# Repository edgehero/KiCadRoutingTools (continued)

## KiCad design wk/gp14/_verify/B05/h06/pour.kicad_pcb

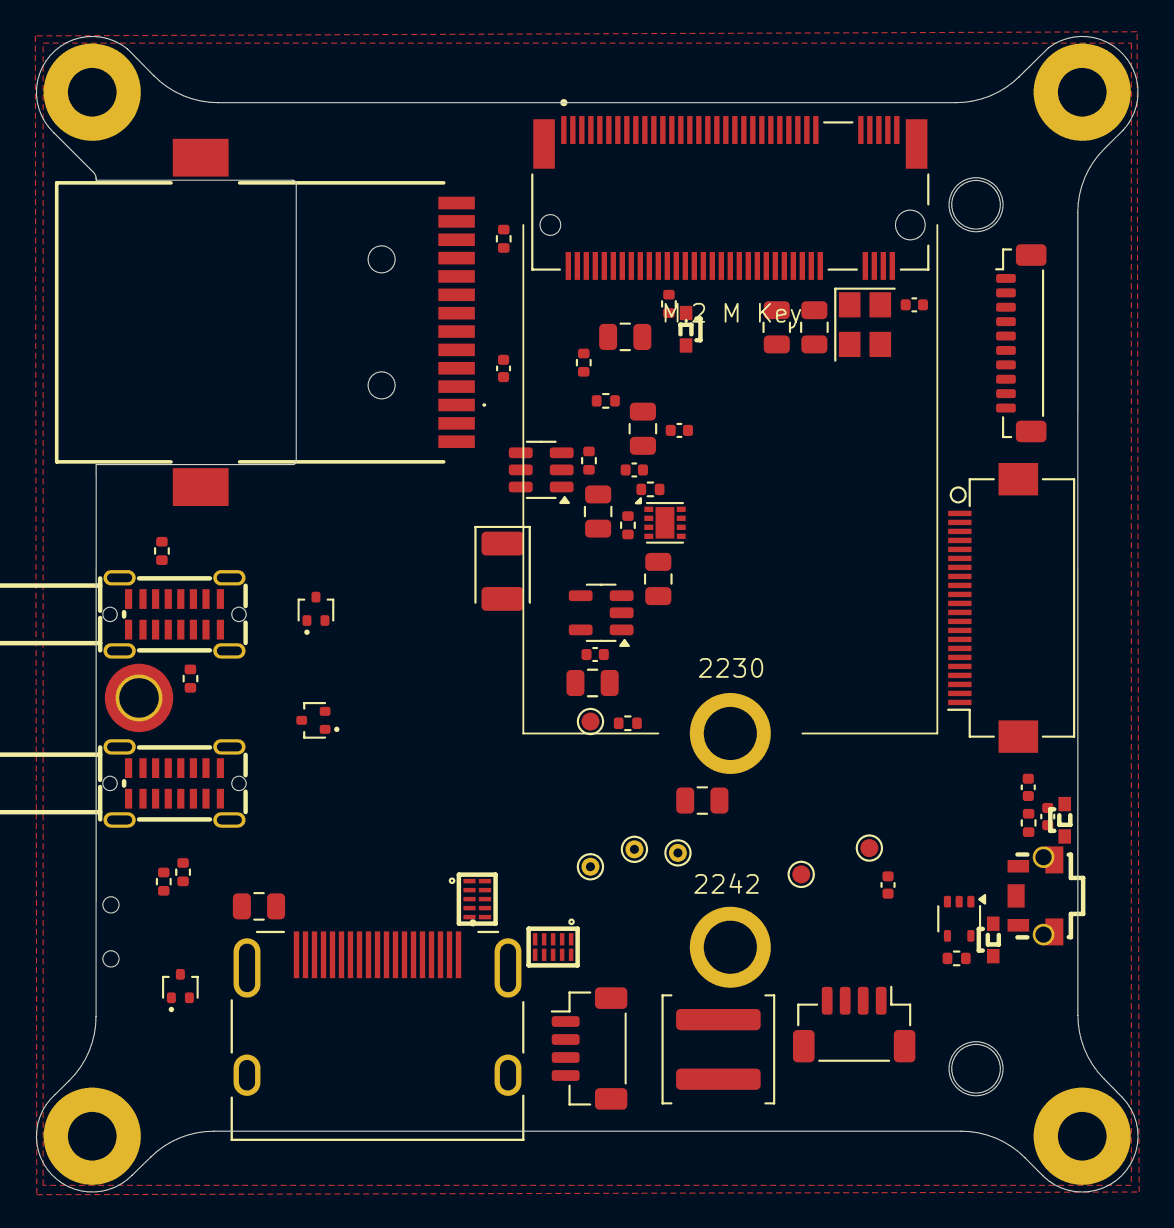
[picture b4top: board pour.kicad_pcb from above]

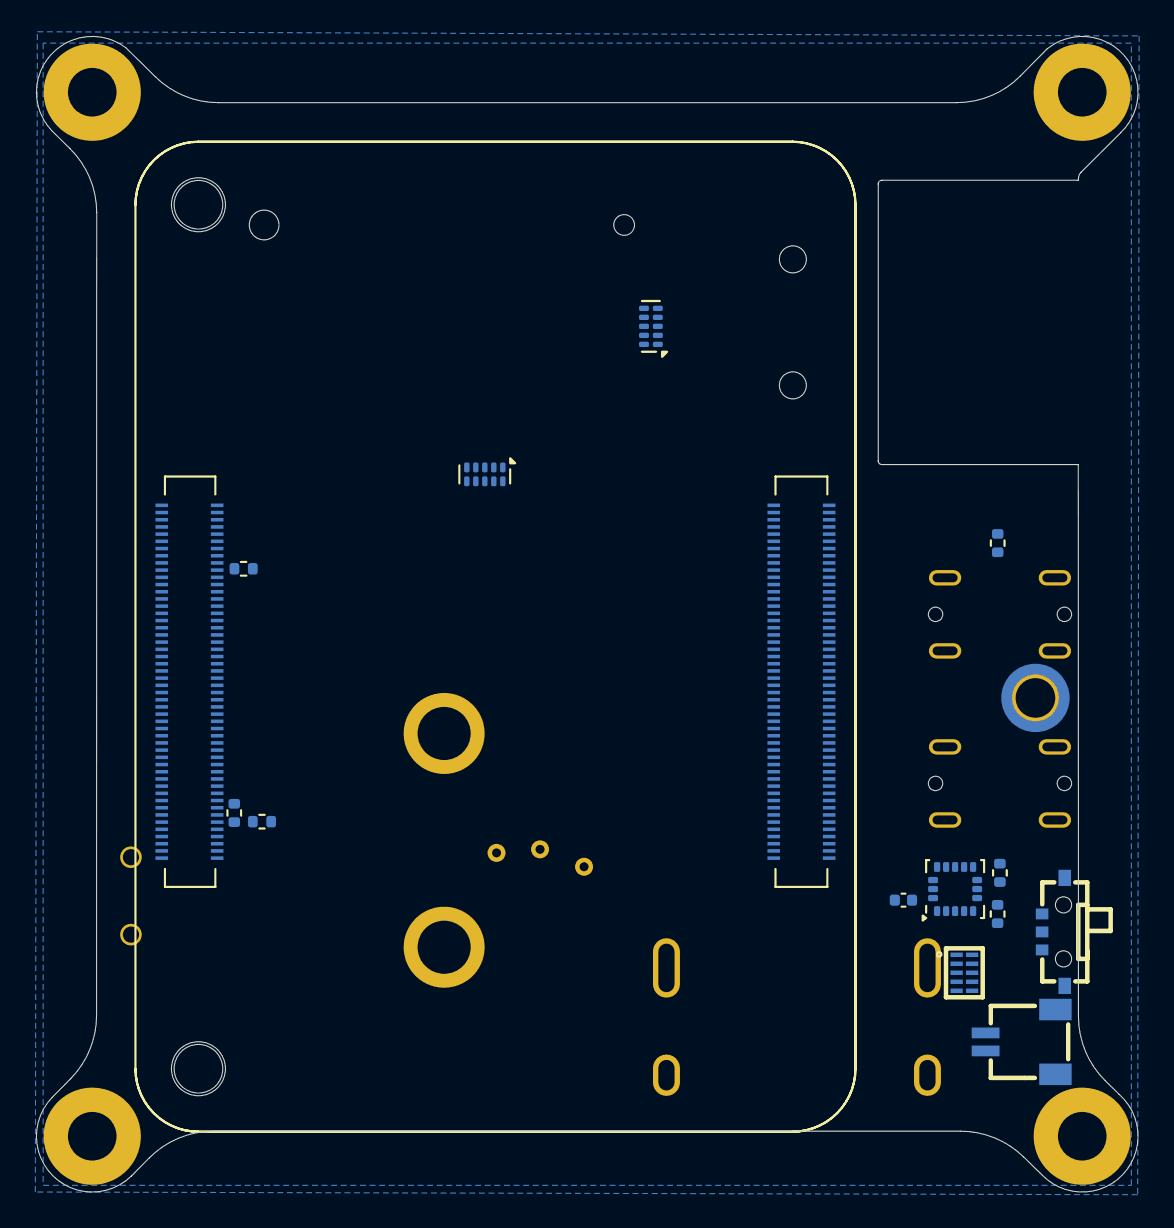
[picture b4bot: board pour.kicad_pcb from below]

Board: 6 copper layers, 61.2 x 64.2 mm, 84 parts (15 on the bottom side), 95 nets, no tracks yet.

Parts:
C101, C102, C401, C501, C502, C503, C706, C712: 100n; C_0402_1005Metric
C601: 4u7; C_0805_2012Metric
C701, C703, C704, C705, C708, C709, C710, C711: 10u; C_0805_2012Metric
C702: 100uF; CP_EIA-3528-21_Kemet-B
C707: 4.7nF; C_0402_1005Metric
CN1: SM02B-SRSS-TB (LF)(SN); CONN-SMD_2P-P1.00_SM02B-SRSS-TB-LF-SN
D101, D502, D701: RCLAMP0502BA; SOT-416
D401, D402, D403: PUSB3F96X; DFN2510A-10_L2.5-W1.0-P0.50-BL
D605, D606, D702: GREEN; LED-SMD_L1.7-W0.6-RD
H101: MountingHole_Pad; MountingHole_2.2mm_M2_DIN965_Pad_TopBottom
H102, H103, H104, H105: MountingHole_Pad; MountingHole_2.7mm_Pad
J1: GLPLX-SMT-188S7; GLPLXSMT188S7QQYG
J101: TYPEC-305-ACP16H458; USB-C-SMD_TYPEC-305-ACP16H458
J501: GT-HD001B-CNNG1; EDAC 690-019-298-412
J502: I2C; JST_SH_BM04B-SRSS-TB_1x04-1MP_P1.00mm_Vertical
J503: SPI; JST_SUR_BM10B-SURS-TF_1x10-1MP_P0.80mm_Vertical
J601: JST_SHBM04B-SRSS-TB; JST_SH_BM04B-SRSS-TB_1x04-1MP_P1.00mm_Vertical
J701: Bus_M.2_Socket_M; M.2 M Key socket_2230_2242
J802: Conn_01x22_Female; Hirose_FH12-22S-0.5SH_1x22-1MP_P0.50mm_Horizontal
L701: 2.2uH; L_Coilcraft_XAL5030-XXX
M701, M702: M.2 Solder Nut; MountingHole_3mm_Pad
Module301: ComputeModule5-CM5; Raspberry-Pi-5-Compute-Module_GPIO
Module302: ComputeModule5-CM5; Raspberry-Pi-5-Compute-Module_HSS
R101, R501, R502, R605, R606, R706, R707: 2k2; R_0402_1005Metric
R102, R103, R403: 0R; R_0402_1005Metric
R104, R107, R108, R705: 10k; R_0402_1005Metric
R401, R402: 470R; R_0402_1005Metric
R701: 15k; R_0402_1005Metric
R702, R703: 22k; R_0402_1005Metric
R704: 100k; R_0402_1005Metric
SW101: MK-11C04-G013; SW-SMD_MK-11C04-G013
SW501: TS-1010A-B; SW-SMD_TS-1010A-B
TP101: VBUS; TestPoint_Pad_D1.0mm
TP102: +5V_PI; TestPoint_Pad_D1.0mm
TP103: +3V3_PI; TestPoint_Pad_D1.0mm
TP104, TP105, TP106: GND; TestPoint_THTPad_D1.0mm_Drill0.5mm
U1: LIS3DH; LGA-16_3x3mm_P0.5mm_LayoutBorder3x5y
U401, U402: TPD4EUSB30; USON-10_2.5x1.0mm_P0.5mm
U405: STMPS2151STR; SOT-23-5
U602: SN74LVC1G14DBVR; SOT-353_SC-70-5
U701: AP22653W6; SOT-23-6
U702: AP3441SHE-7B; DFN-8-1EP_2x2mm_P0.5mm_EP1.05x1.75mm
U703: ASEK-32.768KHZ-L-R-T; Crystal_SMD_3225-4Pin_3.2x2.5mm
USB701: TYPEC-305-ACP16H458; USB-C-SMD_TYPEC-305-ACP16H458

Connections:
+1V8: Module301.88 (+1.8v_(Output)), Module301.90 (+1.8v_(Output)), R103.1
+3V3_PI: C503.1, C601.1, J1.12 (A_GREEN), J1.14 (A_YELLOW), J502.4, J503.1, J802.22, Module301.84 (+3.3v_(Output)), Module301.86 (+3.3v_(Output)), R102.1, R107.2, R501.1, R502.1, TP103.1, U1.1 (VDD_IO), U1.14 (VDD)
+5V: C101.1, C102.1, C501.1, C701.1, C704.1, C705.1, C706.1, D605.2 (A), D606.2 (A), J101.A4 (VBUS), J101.A9 (VBUS), J101.B4 (VBUS), J101.B9 (VBUS), J601.1, Module301.77 (+5v_(Input)), Module301.79 (+5v_(Input)), Module301.81 (+5v_(Input)), Module301.83 (+5v_(Input)), Module301.85 (+5v_(Input)), Module301.87 (+5v_(Input)), R101.1, R702.2, R703.2, TP101.1, TP102.1, U405.4 (EN), U405.5 (VIN), U602.5 (VCC), U701.1 (IN), U702.3 (VIN)
+BATT: CN1.1, Module301.76 (VBAT)
/CC1: J101.A5 (CC1), Module301.94 (CC1)
/CC2: J101.B5 (CC2), Module301.96 (CC2)
/CM5/BL_GPIO24: J503.7, Module301.45 (GPIO24)
/CM5/CAM_GPIO0: J802.17, Module301.97 (CAM_GPIO0)
/CM5/CAM_GPIO1: J802.18, Module301.100 (CAM_GPIO1)
/CM5/CS_GPIO18: J503.5, Module301.49 (GPIO18)
/CM5/DC_GPI25: J503.3, Module301.41 (GPIO25)
/CM5/DPHY0_P.C_N: J802.8, Module302.127 (MIPI0_C_N)
/CM5/DPHY0_P.C_P: J802.9, Module302.129 (MIPI0_C_P)
/CM5/DPHY0_P.D0_N: J802.2, Module302.115 (MIPI0_D0_N)
/CM5/DPHY0_P.D0_P: J802.3, Module302.117 (MIPI0_D0_P)
/CM5/DPHY0_P.D1_N: J802.5, Module302.121 (MIPI0_D1_N)
/CM5/DPHY0_P.D1_P: J802.6, Module302.123 (MIPI0_D1_P)
/CM5/DPHY0_P.D2_N: J802.11, Module302.133 (MIPI0_D2_N)
/CM5/DPHY0_P.D2_P: J802.12, Module302.135 (MIPI0_D2_P)
/CM5/DPHY0_P.D3_N: J802.14, Module302.139 (MIPI0_D3_N)
/CM5/DPHY0_P.D3_P: J802.15, Module302.141 (MIPI0_D3_P)
/CM5/EEPROM_nWP: Module301.20 (EEPROM_nWP), R104.2
/CM5/ETH_PI.TRD0_N: J1.3 (TD1-), Module301.10 (Ethernet_Pair0_N), U401.2 (D1-), U401.9
/CM5/ETH_PI.TRD0_P: J1.2 (TD1+), Module301.12 (Ethernet_Pair0_P), U401.1 (D1+), U401.10
/CM5/ETH_PI.TRD1_N: J1.5 (TD2-), Module301.6 (Ethernet_Pair1_N), U401.5 (D2-), U401.6
/CM5/ETH_PI.TRD1_P: J1.4 (TD2+), Module301.4 (Ethernet_Pair1_P), U401.4 (D2+), U401.7
/CM5/ETH_PI.TRD2_N: J1.7 (TD3-), Module301.9 (Ethernet_Pair2_N), U402.2 (D1-), U402.9
/CM5/ETH_PI.TRD2_P: J1.6 (TD3+), Module301.11 (Ethernet_Pair2_P), U402.1 (D1+), U402.10
/CM5/ETH_PI.TRD3_N: J1.9 (TD4-), Module301.5 (Ethernet_Pair3_N), U402.5 (D2-), U402.6
/CM5/ETH_PI.TRD3_P: J1.8 (TD4+), Module301.3 (Ethernet_Pair3_P), U402.4 (D2+), U402.7
/CM5/ETH_nLED_ACTIVITY: Module301.15 (Ethernet_nLED3(3.3v)), R401.1
/CM5/GPIO_VREF: Module301.78 (GPIO_VREF(1.8v/3.3v_Input)), R102.2, R103.2
/CM5/HDMI_PI.CEC: D403.1 (CH1), D403.10 (NC), J501.13 (CEC), Module302.151 (HDMI0_CEC)
/CM5/HDMI_PI.CK_N: D401.5 (CH4), D401.6 (NC), J501.12 (CK-), Module302.190 (HDMI0_CLK_N)
/CM5/HDMI_PI.CK_P: D401.4 (CH3), D401.7 (NC), J501.10 (CK+), Module302.188 (HDMI0_CLK_P)
/CM5/HDMI_PI.D0_N: D401.2 (CH2), D401.9 (NC), J501.9 (D0-), Module302.184 (HDMI0_TX0_N)
/CM5/HDMI_PI.D0_P: D401.1 (CH1), D401.10 (NC), J501.7 (D0+), Module302.182 (HDMI0_TX0_P)
/CM5/HDMI_PI.D1_N: D402.5 (CH4), D402.6 (NC), J501.6 (D1-), Module302.178 (HDMI0_TX1_N)
/CM5/HDMI_PI.D1_P: D402.4 (CH3), D402.7 (NC), J501.4 (D1+), Module302.176 (HDMI0_TX1_P)
/CM5/HDMI_PI.D2_N: D402.2 (CH2), D402.9 (NC), J501.3 (D2-), Module302.172 (HDMI0_TX2_N)
/CM5/HDMI_PI.D2_P: D402.1 (CH1), D402.10 (NC), J501.1 (D2+), Module302.170 (HDMI0_TX2_P)
/CM5/HDMI_PI.HOTPLUG: D403.2 (CH2), D403.9 (NC), J501.19 (HPD/HEAC-), Module302.153 (HDMI0_HOTPLUG)
/CM5/HDMI_PI.SCL: D403.5 (CH4), D403.6 (NC), J501.15 (SCL), Module302.200 (HDMI0_SCL)
/CM5/HDMI_PI.SDA: D403.4 (CH3), D403.7 (NC), J501.16 (SDA), Module302.199 (HDMI0_SDA)
/CM5/MISO_GPIO19: J503.10, Module301.26 (GPIO19)
/CM5/MOSI_GPIO20: J503.9, Module301.27 (GPIO20)
/CM5/PCIE_PI.CLK_N: J701.53 (REFCLKn), Module302.112 (PCIe_CLK_N)
/CM5/PCIE_PI.CLK_P: J701.55 (REFCLKp), Module302.110 (PCIe_CLK_P)
/CM5/PCIE_PI.PWR_EN: Module302.106 (PCIE_PWR_EN), R704.1, U702.7 (EN)
/CM5/PCIE_PI.RX_N: J701.43 (PETp0), Module302.118 (PCIe_RX_N)
/CM5/PCIE_PI.RX_P: J701.41 (PETn0), Module302.116 (PCIe_RX_P)
/CM5/PCIE_PI.TX_N: J701.49 (PERp0), Module302.124 (PCIe_TX_N)
/CM5/PCIE_PI.TX_P: J701.47 (PERn0), Module302.122 (PCIe_TX_P)
/CM5/PCIE_PI.nCLKREQ: J701.52 (~CLKREQ), Module302.102 (PCIe_nCLKREQ)
/CM5/PCIE_PI.nRST: J701.50 (~PERST), Module302.109 (PCIe_nRST)
/CM5/PCIE_PI.nWAKE: J701.54 (~PEWAKE), Module302.104 (PCIE_nWAKE)
/CM5/PI_nLED_PWR: Module301.95 (LED_nPWR), U602.2
/CM5/PWM: J601.2, Module301.19 (FAN_PWM)
/CM5/PWR_BUT: Module301.92 (PWR_BUT), SW501.1
/CM5/RST_GPIO27: J503.4, Module301.48 (GPIO27)
/CM5/SCL0: J802.20, Module301.80 (SCL0)
/CM5/SCLK_GPIO21: J503.8, Module301.25 (GPIO21)
/CM5/SDA0: J802.21, Module301.82 (SDA0)
/CM5/TACHO: J601.4, Module301.16 (FAN_TACHO)
/CM5/USB2P.D_N: D701.2 (K2), Module302.136 (USB3-0-D_N), USB701.A7 (D-), USB701.B7 (D-)
/CM5/USB2P.D_P: D701.1 (K1), Module302.134 (USB3-0-D_P), USB701.A6 (D+), USB701.B6 (D+)
/CM5/VBUS_EN: Module302.111 (VBUS_EN), U701.3 (EN)
/CM5/nLED_ACTIVITY: Module301.21 (LED_nACT), R606.2
/CM5/nLED_SPEED_100_1000: Module301.17 (Ethernet_nLED2(3.3v)), R402.1
/CM5/nRPIBOOT: Module301.93 (nRPIBOOT), SW101.C
/IO/SCL: D502.1 (K1), J502.2, Module301.56 (GPIO3), R502.2, U1.4 (SPC)
/IO/SDA: D502.2 (K2), J502.1, Module301.58 (GPIO2), R501.2, U1.6 (SDI)
/PCIe-M2/FB: C707.2, R705.2, R706.1, U702.1 (FB)
/PCIe-M2/M2_LX: L701.1, U702.6 (LX)
/USB/CC1: R703.1, USB701.A5 (CC1)
/USB/CC2: R702.1, USB701.B5 (CC2)
/USB_C.D_N: D101.2 (K2), J101.A7 (D-), J101.B7 (D-), Module302.103 (USB2_N)
/USB_C.D_P: D101.1 (K1), J101.A6 (D+), J101.B6 (D+), Module302.105 (USB2_P)
GND: C101.2, C102.2, C401.2, C501.2, C502.2, C503.2, C601.2, C701.2, C702.2, C703.2, C704.2, C705.2, C706.2, C708.2, C709.2, C710.2, C711.2, C712.2, CN1.2, D101.3 (A), D401.3 (GND), D401.8 (GND), D402.3 (GND), D402.8 (GND), D403.3 (GND), D403.8 (GND), D502.3 (A), D701.3 (A), H101.1, H102.1, H103.1, H104.1, H105.1, J1.10 (GND), J101.1 (SHIELD), J101.A1 (GND), J101.A12 (GND), J101.B1 (GND), J101.B12 (GND), J501.2 (D2S), J501.5 (D1S), J501.8 (D0S), J501.11 (CKS), J501.17 (GND), J501.SH1 (SH), J501.SH2 (SH), J501.SH3 (SH), J501.SH4 (SH), J502.3, J503.2, J503.6, J601.3, J701.1 (GND), J701.3 (GND), J701.9 (GND), J701.15 (GND), J701.21 (GND), J701.27 (GND), J701.33 (GND), J701.39 (GND), J701.45 (GND), J701.51 (GND), J701.57 (GND), J701.71 (GND), J701.73 (GND), J701.75 (GND), J701.S1, J701.S2, J802.1, J802.4, J802.7, J802.10, J802.13, J802.16, J802.19, Module301.1 (GND), Module301.2 (GND), Module301.7 (GND), Module301.8 (GND), Module301.13 (GND), Module301.14 (GND), Module301.22 (GND), Module301.23 (GND), Module301.32 (GND), Module301.33 (GND), Module301.42 (GND), Module301.43 (GND), Module301.52 (GND), Module301.53 (GND), Module301.59 (GND), Module301.60 (GND), Module301.65 (GND), Module301.66 (GND), Module301.71 (GND), Module301.74 (GND), Module301.98 (GND), Module302.107 (GND), Module302.108 (GND), Module302.113 (GND), Module302.114 (GND), Module302.119 (GND), Module302.120 (GND), Module302.125 (GND), Module302.126 (GND), Module302.131 (GND), Module302.132 (GND), Module302.137 (GND), Module302.138 (GND), Module302.144 (GND), Module302.150 (GND), Module302.155 (GND), Module302.156 (GND), Module302.161 (GND), Module302.162 (GND), Module302.167 (GND), Module302.168 (GND), Module302.173 (GND), Module302.174 (GND), Module302.179 (GND), Module302.180 (GND), Module302.185 (GND), Module302.186 (GND), Module302.191 (GND), Module302.192 (GND), Module302.197 (GND), Module302.198 (GND), R101.2, R104.1, R108.1, R403.2, R701.2, R704.2, R706.2, SW101.1, SW101.4, SW101.5, SW501.2, SW501.3, SW501.4, SW501.5, TP104.1, TP105.1, TP106.1, U1.5 (GND), U1.10 (RES), U1.12 (GND), U401.3 (GND), U401.8 (GND), U402.3 (GND), U402.8 (GND), U405.2 (GND), U602.3 (GND), U701.2 (GND), U702.4 (PGND), U702.8 (SGND), U702.9 (PAD), U703.2 (GND), USB701.1 (EP), USB701.A1 (GND), USB701.A12 (GND), USB701.B1 (GND), USB701.B12 (GND)
HDMI_+5V: C502.1, J501.18 (+5V), U405.1 (VOUT)
M2_3V3: C707.1, C708.1, C709.1, C710.1, C711.1, C712.1, D702.2 (A), J701.2 (3.3V), J701.4 (3.3V), J701.12 (3.3V), J701.14 (3.3V), J701.16 (3.3V), J701.18 (3.3V), J701.70 (3.3V), J701.72 (3.3V), J701.74 (3.3V), L701.2, R705.1, U703.1 (EN), U703.4 (VDD)
unnamed: D605.1 (K), R605.1
unnamed: D606.1 (K), R606.1
unnamed: D702.1 (K), R707.1
unnamed: J1.11 (K_GREEN), R401.2
unnamed: J1.13 (K_YELLOW), R402.2
unnamed: J1.15 (MP1), J1.16 (MP2), R403.1
unnamed: C401.1, J1.1 (VCC)
unnamed: J701.10 (DAS/~DSS/~LED1), R707.2
unnamed: J701.68 (SUSCLK), U703.3 (Out)
unnamed: R605.2, U602.4
unnamed: R107.1, U1.8 (CS)
unnamed: R108.2, U1.7 (SDO)
unnamed: R701.1, U701.5 (ILIM)
VBUS_USB2.0: C702.1, C703.1, U701.6 (OUT), USB701.A4 (VBUS), USB701.A9 (VBUS), USB701.B4 (VBUS), USB701.B9 (VBUS)

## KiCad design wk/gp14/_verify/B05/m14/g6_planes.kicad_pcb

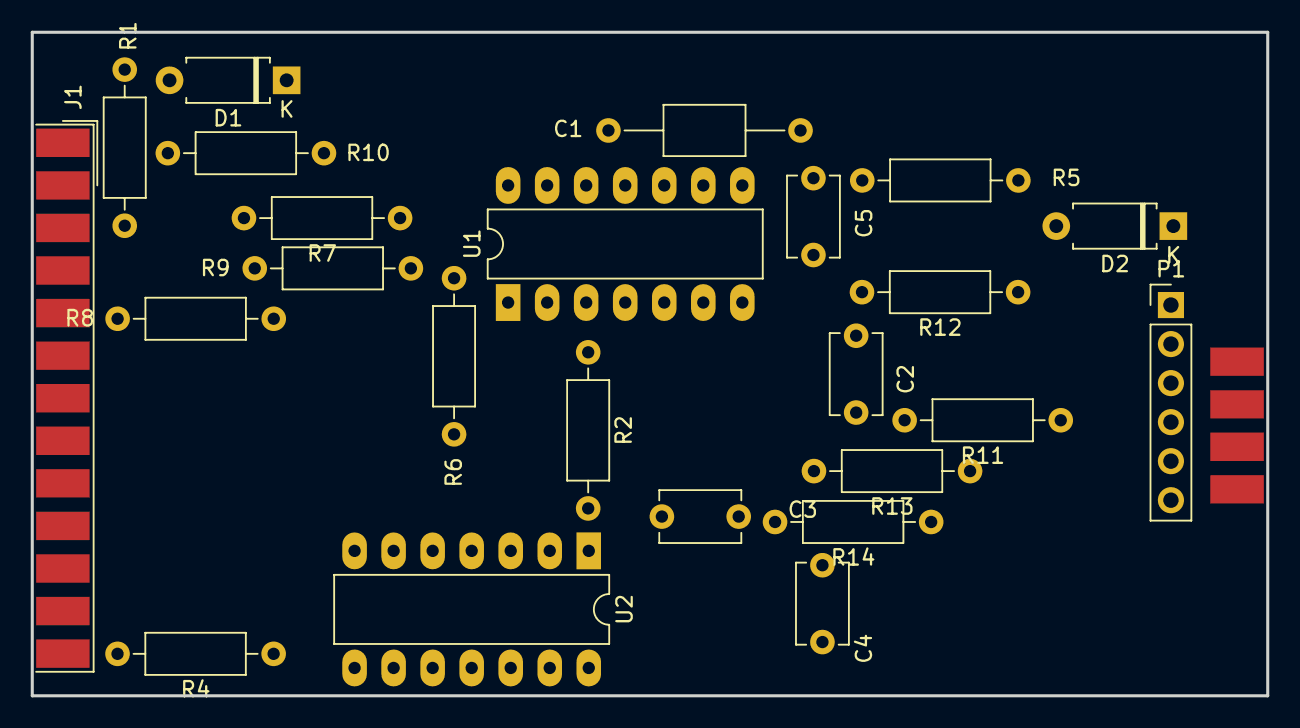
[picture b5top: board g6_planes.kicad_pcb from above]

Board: 2 copper layers, 80.4 x 43.2 mm, 25 parts (1 on the bottom side), 26 nets, no tracks yet.

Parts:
C1: 1uF; C_Axial_L5.1mm_D3.1mm_P12.50mm_Horizontal
C2, C3, C4, C5: 100pF; C_Disc_D5.1mm_W3.2mm_P5.00mm
D1, D2: BAT46; D_A-405_P7.62mm_Horizontal
J1: DB25MALE; DSUB-25_Male_EdgeMount_P2.77mm
J2: DB9MALE; DSUB-9_Male_EdgeMount_P2.77mm
P1: CONN_6; PinHeader_1x06_P2.54mm_Vertical
R1, R6, R7, R8, R9, R10, R11, R12, R13, R14: 100; R_Axial_DIN0207_L6.3mm_D2.5mm_P10.16mm_Horizontal
R2: 5,1K; R_Axial_DIN0207_L6.3mm_D2.5mm_P10.16mm_Horizontal
R4: 47; R_Axial_DIN0207_L6.3mm_D2.5mm_P10.16mm_Horizontal
R5: 1K; R_Axial_DIN0207_L6.3mm_D2.5mm_P10.16mm_Horizontal
U1, U2: 74LS125; DIP-14_W7.62mm_LongPads

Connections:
/CLK-D1: J1.3, R10.2
/CTRL-D3: J1.5, R8.2
/DONE-SELECT*: J1.13, R4.2
/PWR_3,3-5V: D2.1 (A), J2.1, P1.1
/TCK-CCLK: J2.4, P1.5, R12.1
/TD0-DONE: J2.2, P1.3, R14.1
/TD0-PROG-D4: J1.6, R6.2
/TDI-DIN: J2.3, P1.4, R11.1
/TDI-DIN-D0: J1.2, R7.2
/TMS-PROG: J2.5, P1.6, R13.1
/TMS-PROG-D2: J1.4, R9.2
/VCC_SENSE-ERROR*: J1.15, R1.2
GND: C1.2, C2.2, C3.2, C4.2, C5.2, J1.20, J1.25, J2.6, J2.7, J2.8, J2.9, P1.2, R5.2, U1.2 (D), U1.7 (GND), U2.1 (E), U2.4 (E), U2.5 (D), U2.7 (GND), U2.9 (D), U2.10 (E), U2.12 (D), U2.13 (E)
unnamed: D1.2 (K), R1.1
unnamed: J1.8, J1.11, J1.12
unnamed: R6.1, U1.1 (E)
unnamed: C3.1, R2.2, R14.2, U1.3 (O), U2.2 (D)
unnamed: R7.1, U1.5 (D)
unnamed: R8.1, U1.4 (E), U1.10 (E), U1.13 (E)
unnamed: C2.1, R11.2, U1.6 (O)
unnamed: R10.1, U1.9 (D)
unnamed: C5.1, R12.2, U1.8 (O)
unnamed: R9.1, U1.12 (D)
unnamed: C4.1, R13.2, U1.11 (O)
unnamed: R4.1, U2.3 (O)
VCC: C1.1, D1.1 (A), D2.2 (K), R2.1, R5.1, U1.14 (VCC), U2.14 (VCC)

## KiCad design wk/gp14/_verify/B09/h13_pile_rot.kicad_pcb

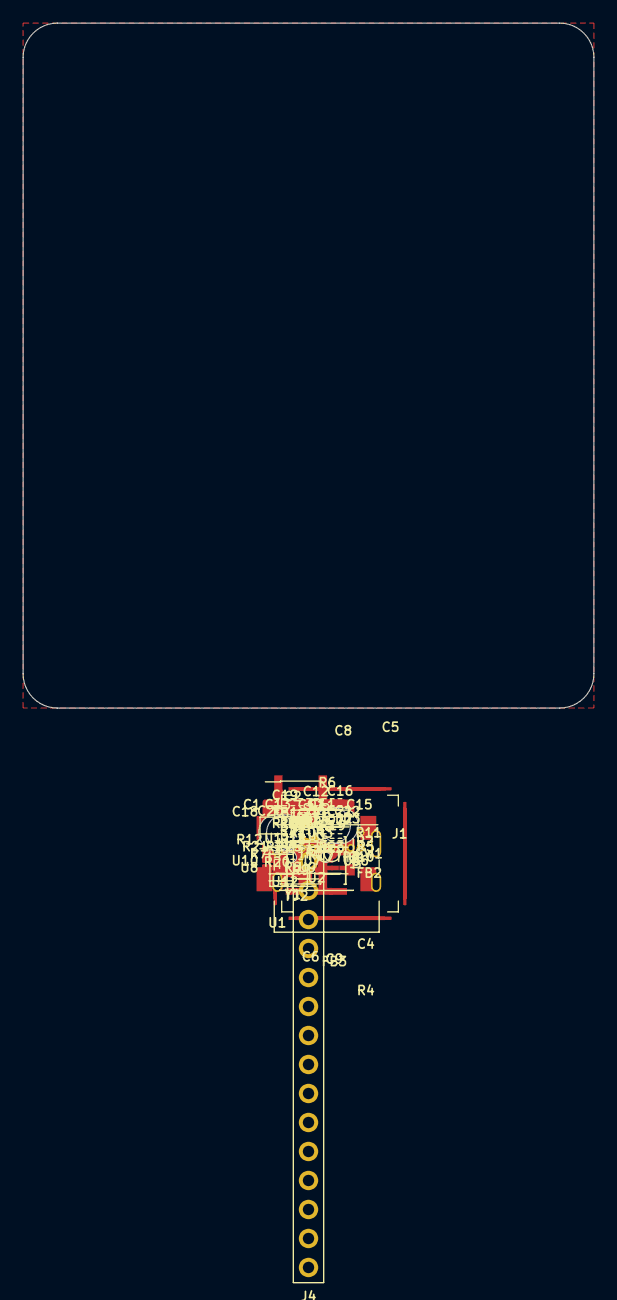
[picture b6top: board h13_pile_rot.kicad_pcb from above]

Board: 2 copper layers, 50.0 x 60.0 mm, 84 parts (0 on the bottom side), 61 nets, no tracks yet.

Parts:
C1, C2, C5, C6, C7, C17: 4u7; C_0603_1608Metric
C3, C4: 27pF; C_0603_1608Metric
C8, C9, C10, C11, C12, C13, C14, C15, C16, C18, C19, C20, C21, C22: 100nF; C_0603_1608Metric
D1, D2, D3, D4, D5, D6: LED; LED_0603_1608Metric
FB1, FB2, FB3: Ferrite_Bead; L_0603_1608Metric
FID1, FID2, FID3: Fiducial; Fiducial_1mm_Mask2mm
H1, H2, H3, H4: MountingHole; MountingHole_3.2mm_M3
J1: USB_C_Receptacle_USB2.0; USB_C_Receptacle_GCT_USB4085
J2: Conn_ST_STDC14; PinHeader_2x07_P1.27mm_Vertical_SMD
J4: Conn_01x16; PinHeader_1x16_P2.54mm_Vertical
Q1: 2N7002; SOT-23
R1, R2: 5k1; R_0603_1608Metric
R3, R6, R17, R22, R23, R24: 10k; R_0603_1608Metric
R4: 12k; R_0603_1608Metric
R5: 2k; R_0603_1608Metric
R7, R8, R9, R10, R18, R21: 1k; R_0603_1608Metric
R11, R12, R13, R14, R15, R16, R19, R20: 100R; R_0603_1608Metric
R25: 100k; R_0603_1608Metric
SW1: SW_SPDT; SW_SPDT_PCM12
SW2: SW_Push; SW_Push_1P1T_NO_E-Switch_TL3301NxxxxxG
TP1, TP2: TestPoint; TestPoint_Pad_D1.0mm
U1: FT2232HL; LQFP-64_10x10mm_P0.5mm
U2: XC6206PxxxMR; SOT-23
U3: SRV05-4; SOT-23-6
U4: 93LCxxB; SOIC-8_3.9x4.9mm_P1.27mm
U5, U7, U8, U9, U10, U11, U12: 74LVC1G125; SOT-353_SC-70-5
U6: 74LVC1G126; SOT-353_SC-70-5
Y1: Crystal_GND24; Crystal_SMD_3225-4Pin_3.2x2.5mm

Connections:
+1V8: C7.1, C10.1, C11.1, C12.1, U1.12 (VCORE), U1.37 (VCORE), U1.49 (VREGOUT), U1.64 (VCORE)
+3V3: C2.1, C13.1, C14.1, C15.1, C16.1, C18.1, C22.1, D1.2 (A), D2.2 (A), D3.2 (A), D4.2 (A), FB2.2, FB3.2, J4.1, R6.2, R18.1, R23.2, U1.20 (VCCIO), U1.31 (VCCIO), U1.42 (VCCIO), U1.50 (VREGIN), U1.56 (VCCIO), U2.2 (VO), U4.8 (VCC), U5.5 (VCC), U6.5 (VCC), U11.5 (VCC)
+5V: C1.1, FB1.1, U2.3 (VI)
/ACT_LED_K: D1.1 (K), R7.2
/ACT_LED_N: R7.1, U1.21 (ADBUS4)
/CTS_N: TP2.1, U1.41 (BDBUS3)
/EE_CLK: U1.62 (EECLK), U4.2 (SCLK)
/EE_CS: R3.1, U1.63 (EECS), U4.1 (CS)
/EE_DATA: R5.2, U1.61 (EEDATA), U4.3 (DI)
/EE_DO: R5.1, U4.4 (DO)
/GPIO_A: J4.12, U1.27 (ACBUS1)
/GPIO_B: J4.13, U1.28 (ACBUS2)
/GPIO_C: J4.14, U1.32 (ACBUS5)
/GPIO_D: J4.15, U1.33 (ACBUS6)
/OSCI: C3.1, U1.2 (OSCI), Y1.1
/OSCO: C4.1, U1.3 (OSCO), Y1.3
/PWR_LED_A: D5.2 (A), R18.2
/REF: R4.1, U1.6 (REF)
/RESET_N: R6.1, U1.14 (~RESET)
/RTS_N: TP1.1, U1.40 (BDBUS2)
/RXD: U1.39 (BDBUS1), U11.4
/RXD_IN: R25.1, SW1.2 (B), U11.2
/RXD_R: R20.1, SW1.3 (C)
/RXD_TRGT: J2.14 (VCP_TX), J4.11, R20.2
/RX_LED_K: D2.1 (K), R8.1
/RX_LED_N: R8.2, U1.54 (BCBUS3)
/SRST: Q1.1 (G), R24.2, U1.24 (ADBUS7)
/SRST_N_R: Q1.3 (D), R12.2, R17.1, SW2.1
/SRST_N_TRGT: J2.12 (~RST), J4.8, R12.1
/SWDIO_OE_N: R23.1, U1.23 (ADBUS6), U10.1
/SWD_EN: R21.2, R22.2, U1.22 (ADBUS5), U5.1, U6.1, U8.1, U9.1
/SWD_EN_LED: D6.2 (A), R21.1
/TCK: U1.16 (ADBUS0), U7.2
/TCK_R: R13.2, U7.4
/TCK_TRGT: J2.6 (JCLK/SWCLK), J4.4, R13.1
/TDI: U1.17 (ADBUS1), U8.2, U10.2
/TDI_R: R16.2, U8.4
/TDI_TRGT: J2.10 (JTDI/NC), J4.5, R16.1
/TDO: U1.18 (ADBUS2), U5.4, U6.4
/TDO_R: R15.2, SW1.1 (A), U5.2
/TDO_TRGT: J2.8 (JTDO/SWO), J4.6, R15.1
/TMS: U1.19 (ADBUS3), U9.2
/TMS_R: R14.2, U6.2, U9.4, U10.4
/TMS_TRGT: J2.4 (JTMS/SWDIO), J4.7, R14.1
/TXD: U1.38 (BDBUS0), U12.2
/TXD_R: R19.2, U12.4
/TXD_TRGT: J2.13 (VCP_RX), J4.10, R19.1
/TX_LED_K: D3.1 (K), R9.1
/TX_LED_N: R9.2, U1.55 (BCBUS4)
/USB_CC1: J1.A5 (CC1), R2.1, U3.4 (IO3)
/USB_CC2: J1.B5 (CC2), R1.1, U3.3 (IO2)
/USB_DM: J1.A7 (D-), J1.B7 (D-), U1.7 (DM), U3.6 (IO4)
/USB_DP: J1.A6 (D+), J1.B6 (D+), U1.8 (DP), U3.1 (IO1)
/USB_LED_K: D4.1 (K), R10.1
/USB_LED_N: R10.2, U1.60 (~PWREN)
/VDRIVE_TRGT: J2.3 (VCC), J4.2, R11.1
/VPHY: C6.1, C9.1, FB3.1, U1.4 (VPHY)
/VPLL: C5.1, C8.1, FB2.1, U1.9 (VPLL)
GND: C1.2, C2.2, C3.2, C4.2, C5.2, C6.2, C7.2, C8.2, C9.2, C10.2, C11.2, C12.2, C13.2, C14.2, C15.2, C16.2, C17.2, C18.2, C19.2, C20.2, C21.2, C22.2, D5.1 (K), D6.1 (K), J1.A1 (GND), J1.A12 (GND), J1.B1 (GND), J1.B12 (GND), J1.S1 (SHIELD), J2.5 (GND), J2.7 (GND), J2.11 (GNDDetect), J4.3, J4.9, J4.16, Q1.2 (S), R1.2, R2.2, R3.2, R4.2, R22.1, R24.1, SW2.2, U1.1 (GND), U1.5 (GND), U1.10 (AGND), U1.11 (GND), U1.13 (TEST), U1.15 (GND), U1.25 (GND), U1.35 (GND), U1.47 (GND), U1.51 (GND), U2.1 (GND), U3.2 (VN), U4.5 (GND), U5.3 (GND), U6.3 (GND), U7.1, U7.3 (GND), U8.3 (GND), U9.3 (GND), U10.3 (GND), U11.1, U11.3 (GND), U12.1, U12.3 (GND), Y1.2, Y1.4
VBUS: FB1.2, J1.A4 (VBUS), J1.A9 (VBUS), J1.B4 (VBUS), J1.B9 (VBUS), U3.5 (VP)
Vdrive: C17.1, C19.1, C20.1, C21.1, R11.2, R17.2, R25.2, U7.5 (VCC), U8.5 (VCC), U9.5 (VCC), U10.5 (VCC), U12.5 (VCC)

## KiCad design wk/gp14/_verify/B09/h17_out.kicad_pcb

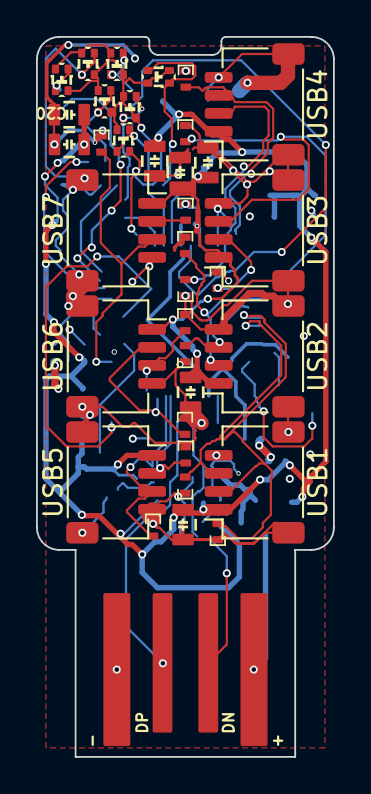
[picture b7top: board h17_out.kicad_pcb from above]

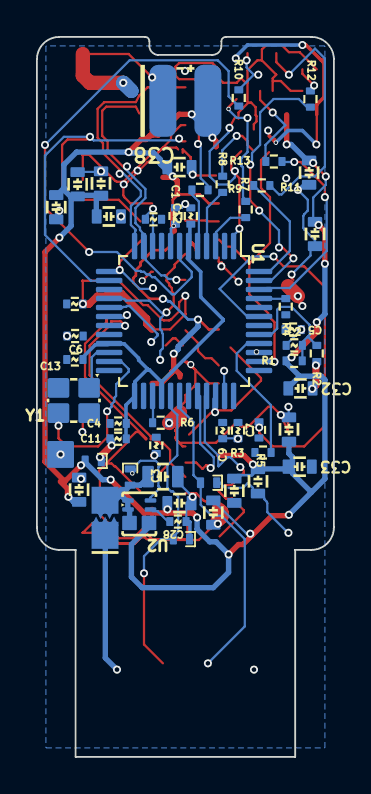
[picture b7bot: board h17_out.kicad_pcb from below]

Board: 2 copper layers, 16.5 x 40.0 mm, 90 parts (53 on the bottom side), 45 nets.

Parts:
C1: 1uF 10V; 1005_C
C2, C5, C6, C7, C8, C9, C10, C11, C12, C13: 0.1uF; 1005_C
C3, C4: 10uF 6.3V; 1005_C
C14, C15, C16, C17, C18, C19, C20, C21: 0.1uF 100V; 2012_C
C22, C23, C24, C25, C26, C27, C29, C30, C31, C32, C33, C34, C35, C36, C37: 22uF 10V; 1608_C
C28: 15nF; 1005_C
C38: 330uF 10V; CP_Elec_6.3x11_Board_Edge_Mirrored
D1, D2, D3, D4, D5, D6, D7, D8, D9, D10, D11, D12, D13, D14, D22, D23: TVS; D_0402
D15, D16, D17, D18, D19, D20, D21: USB; Duo_LED_1.6x0.8_Kingbright_APHB1608LZGKSURKC
D24, D25: 5V; D_0402
H1: Strap; Plain_Hole_3mm
J1: HOST; USB_A_PCB_traces_small
J2: USB1; JST_SH_SM04B-SRSS-TB_1x04-1MP_P1.00mm_Horizontal
J3: USB2; JST_SH_SM04B-SRSS-TB_1x04-1MP_P1.00mm_Horizontal
J4: USB3; JST_SH_SM04B-SRSS-TB_1x04-1MP_P1.00mm_Horizontal
J5: USB4; JST_SH_SM04B-SRSS-TB_1x04-1MP_P1.00mm_Horizontal
J6: USB5; JST_SH_SM04B-SRSS-TB_1x04-1MP_P1.00mm_Horizontal
J7: USB6; JST_SH_SM04B-SRSS-TB_1x04-1MP_P1.00mm_Horizontal
J8: USB7; JST_SH_SM04B-SRSS-TB_1x04-1MP_P1.00mm_Horizontal
J9: EXTGND; 1P-1.5x1.5
JP1: EXTPWR; JP-2_1.5x1.5
R1: 10k; R_1005_C
R2, R3, R4, R5: 100k; R_1005_C
R6: 2.7k; R_1005_C
R7, R8, R9, R10, R11, R12, R13: 470; R_1005_C
U1: MaxLinear_XR22417-48; LQFP-48_7x7mm_P0.5mm
U2: Dialog_SLG5NT1487V; TDFN-8_1.5x2mm_Fused-Lead_JEDEC_MO-252_W2015D
Y1: 12MHz 50ppm 16-20pF; Crystal_4-SMD_2.5x2mm

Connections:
+1V8: C4.1, C11.1, C12.1, C13.1, U1.6 (VCC18), U1.21 (VCC18), U1.25 (1V8_OUT), U1.28 (VCC18)
+3.3V: C3.1, C5.1, C6.1, C7.1, C8.1, C9.1, C10.1, R3.1, R4.1, R5.1, U1.9 (3V3_OUT), U1.15 (VCC33), U1.20 (VCC33), U1.26 (VCC33), U1.31 (VCC33), U1.36 (VCC33), U1.42 (VCC33)
+5V: C1.1, C14.1, C15.1, C16.1, C17.1, C18.1, C19.1, C20.1, C22.1, C23.1, C24.1, C25.1, C26.1, C27.1, C29.1, C30.1, C31.1, C32.1, C33.1, C34.1, C35.1, C36.1, C37.1, C38.1 (+), D25.2 (A2), J2.1, J3.1, J4.1, J5.1, J6.1, J7.1, J8.1, R1.1, U1.8 (VCC5), U2.5 (S)
/D+: D23.2 (A2), J1.3, U1.30 (UP_D+)
/D-: D22.2 (A2), J1.2, U1.29 (UP_D-)
/LC: D15.GK (2), D15.RA (3), D16.GK (2), D16.RA (3), D17.GK (2), D17.RA (3), D18.GK (2), D18.RA (3), D19.GK (2), D19.RA (3), D20.GK (2), D20.RA (3), D21.GK (2), D21.RA (3), U1.1 (LED_CTL)
/LED1: R7.2, U1.3 (LED1/SCL)
/LED2: R8.2, U1.4 (LED2)
/LED3: R9.2, U1.5 (LED3)
/LED4: R10.2, U1.7 (LED4)
/LED5: R11.2, U1.48 (LED5)
/LED6: R12.2, U1.47 (LED6)
/LED7: R13.2, U1.46 (LED7)
/U1D+: D2.2 (A2), J2.3, U1.19 (USB1D+)
/U1D-: D1.2 (A2), J2.2, U1.18 (USB1D-)
/U2D+: D4.2 (A2), J3.3, U1.17 (USB2D+)
/U2D-: D3.2 (A2), J3.2, U1.16 (USB2D-)
/U3D+: D6.2 (A2), J4.3, U1.14 (USB3D+)
/U3D-: D5.2 (A2), J4.2, U1.13 (USB3D-)
/U4D+: D8.2 (A2), J5.3, U1.12 (USB4D+)
/U4D-: D7.2 (A2), J5.2, U1.11 (USB4D-)
/U5D+: D10.2 (A2), J6.3, U1.33 (USB5D+)
/U5D-: D9.2 (A2), J6.2, U1.32 (USB5D-)
/U6D+: D12.2 (A2), J7.3, U1.35 (USB6D+)
/U6D-: D11.2 (A2), J7.2, U1.34 (USB6D-)
/U7D+: D14.2 (A2), J8.3, U1.38 (USB7D+)
/U7D-: D13.2 (A2), J8.2, U1.37 (USB7D-)
/XI: U1.22 (XTALIN), Y1.1
/XO: U1.23 (XTALOUT), Y1.3
GND: C1.2, C2.2, C3.2, C4.2, C5.2, C6.2, C7.2, C8.2, C9.2, C10.2, C11.2, C12.2, C13.2, C14.2, C15.2, C16.2, C17.2, C18.2, C19.2, C20.2, C21.2, C22.2, C23.2, C24.2, C25.2, C26.2, C27.2, C28.2, C29.2, C30.2, C31.2, C32.2, C33.2, C34.2, C35.2, C36.2, C37.2, C38.2 (-), D1.1 (A1), D2.1 (A1), D3.1 (A1), D4.1 (A1), D5.1 (A1), D6.1 (A1), D7.1 (A1), D8.1 (A1), D9.1 (A1), D10.1 (A1), D11.1 (A1), D12.1 (A1), D13.1 (A1), D14.1 (A1), D22.1 (A1), D23.1 (A1), D24.1 (A1), D25.1 (A1), J1.4, J2.4, J2.MP (MountPin), J3.4, J3.MP (MountPin), J4.4, J4.MP (MountPin), J5.4, J5.MP (MountPin), J6.4, J6.MP (MountPin), J7.4, J7.MP (MountPin), J8.4, J8.MP (MountPin), J9.1, R2.2, R6.2, U1.10 (GND), U1.24 (GND), U1.39 (GND), U2.8 (GND), Y1.2 (GND), Y1.4 (GND)
unnamed: D15.GA (1), D15.RK (4), R7.1
unnamed: D16.GA (1), D16.RK (4), R8.1
unnamed: D17.GA (1), D17.RK (4), R9.1
unnamed: D18.GA (1), D18.RK (4), R10.1
unnamed: D19.GA (1), D19.RK (4), R11.1
unnamed: D20.GA (1), D20.RK (4), R12.1
unnamed: D21.GA (1), D21.RK (4), R13.1
unnamed: J1.1, JP1.1
unnamed: R3.2, U1.40 (EXT_RST#)
unnamed: R6.1, U1.27 (REXT)
unnamed: R5.2, U1.43 (TEST1#)
unnamed: R4.2, U1.45 (TEST3#)
unnamed: C2.1, R1.2, R2.1, U1.41 (VBUS_SENSE)
unnamed: C28.1, U2.7 (CAP)
VIN: C21.1, D24.2 (A2), JP1.2, U2.1 (VDD), U2.2 (ON), U2.3 (D)
